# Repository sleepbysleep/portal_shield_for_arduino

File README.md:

# portal_shield_for_arduino
1xRelay and 2xMOSFET

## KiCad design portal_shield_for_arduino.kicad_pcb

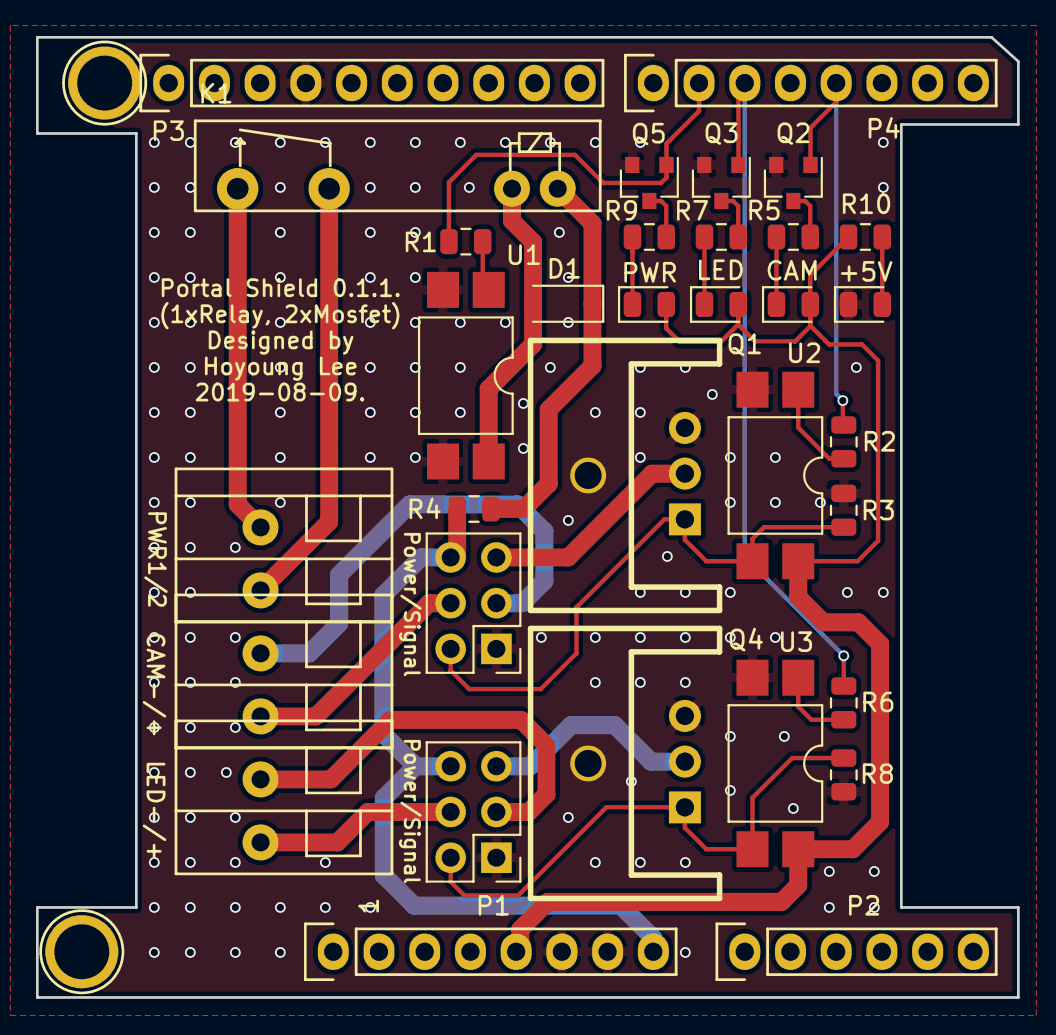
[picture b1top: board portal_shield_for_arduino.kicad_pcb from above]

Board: 2 copper layers, 54.5 x 53.3 mm, 35 parts (0 on the bottom side), 30 nets.

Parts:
+5V: 5V_LED; LED_0805_2012Metric
CAM: CAM_LED; LED_0805_2012Metric
D1: 1N4148W; D_SOD-123
J1: ATX_BTN_CONN; TerminalBlock_Phoenix_PTSA-1,5-2-3.5-Z_1x2_P3.5mm_Vertical
J2: CAMERA_CONFIG; PinHeader_2x03_P2.54mm_Vertical
J3: CAMERA_CONN; TerminalBlock_Phoenix_PTSA-1,5-2-3.5-Z_1x2_P3.5mm_Vertical
J4: LIGHT_CONFIG; PinHeader_2x03_P2.54mm_Vertical
J5: LIGHT_CONN; TerminalBlock_Phoenix_PTSA-1,5-2-3.5-Z_1x2_P3.5mm_Vertical
K1: Relay_Panasonic_PA1a_XX_DIP; Relay_Panasonic_PA1a_xx_DIP
LED: LIGHT_LED; LED_0805_2012Metric
P1: Power; Socket_Strip_Arduino_1x08
P2: Analog; Socket_Strip_Arduino_1x06
P3: Digital; Socket_Strip_Arduino_1x10
P4: Digital; Socket_Strip_Arduino_1x08
P5, P7: CONN_01X01; Arduino_1pin
PWR: LIGHT_LED; LED_0805_2012Metric
Q1, Q4: STP16NF06L; TO220_3_DH15A_HEATSINK
Q2, Q3, Q5: BSS123LT1; SOT-23
R1, R2, R5, R6, R7, R9, R10: 1K; R_0805_2012Metric
R3, R8: 10K; R_0805_2012Metric
R4: 330; R_0805_2012Metric
U1, U2, U3: LTV-817S; SMDIP-4_W9.53mm

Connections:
+5V: CAM.2, LED.2, P1.5, PWR.2, R10.1, U2.4, U3.4
/3(**): P4.5, Q2.1, R2.2
/5(**): P4.3, Q3.1, R6.2
/6(**): P4.2, Q5.1, R1.2
/A4(SDA): P2.5, P3.2
/A5(SCL): P2.6, P3.1
/Vin(12V): J2.6, J4.6, P1.8, R4.1
GND: +5V.1, J2.1, J4.1, P1.6, P1.7, P3.4, Q1.3, Q2.2, Q3.2, Q4.3, Q5.2, R3.2, R8.2, U1.2, U1.3, U2.2, U3.2
unnamed: D1.1, K1.1, R4.2
unnamed: D1.2, K1.2, U1.4
unnamed: CAM.1, R5.2
unnamed: LED.1, R7.1
unnamed: PWR.1, R9.1
unnamed: +5V.2, R10.2
unnamed: J1.1, K1.5
unnamed: J1.2, K1.6
unnamed: J2.2, Q1.1, R3.1, U2.3
unnamed: J2.3, J3.2
unnamed: J2.4, J3.1
unnamed: J2.5, Q1.2
unnamed: J4.2, Q4.1, R8.1, U3.3
unnamed: J4.3, J5.2
unnamed: J4.4, J5.1
unnamed: J4.5, Q4.2
unnamed: Q2.3, R5.1
unnamed: Q3.3, R7.2
unnamed: Q5.3, R9.2
unnamed: R1.1, U1.1
unnamed: R2.1, U2.1
unnamed: R6.1, U3.1

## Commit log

2019-08-13 modified to ease the connection of DSUB9, and add labels for terminals
